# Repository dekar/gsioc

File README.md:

# gsioc
OpenHW Gilson GSIOC controller

This controller is an easier method to connect your Gilson GSIOC devices with PC.

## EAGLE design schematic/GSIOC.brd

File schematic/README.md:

File in Cadsoft Eagle format
ver 0.5

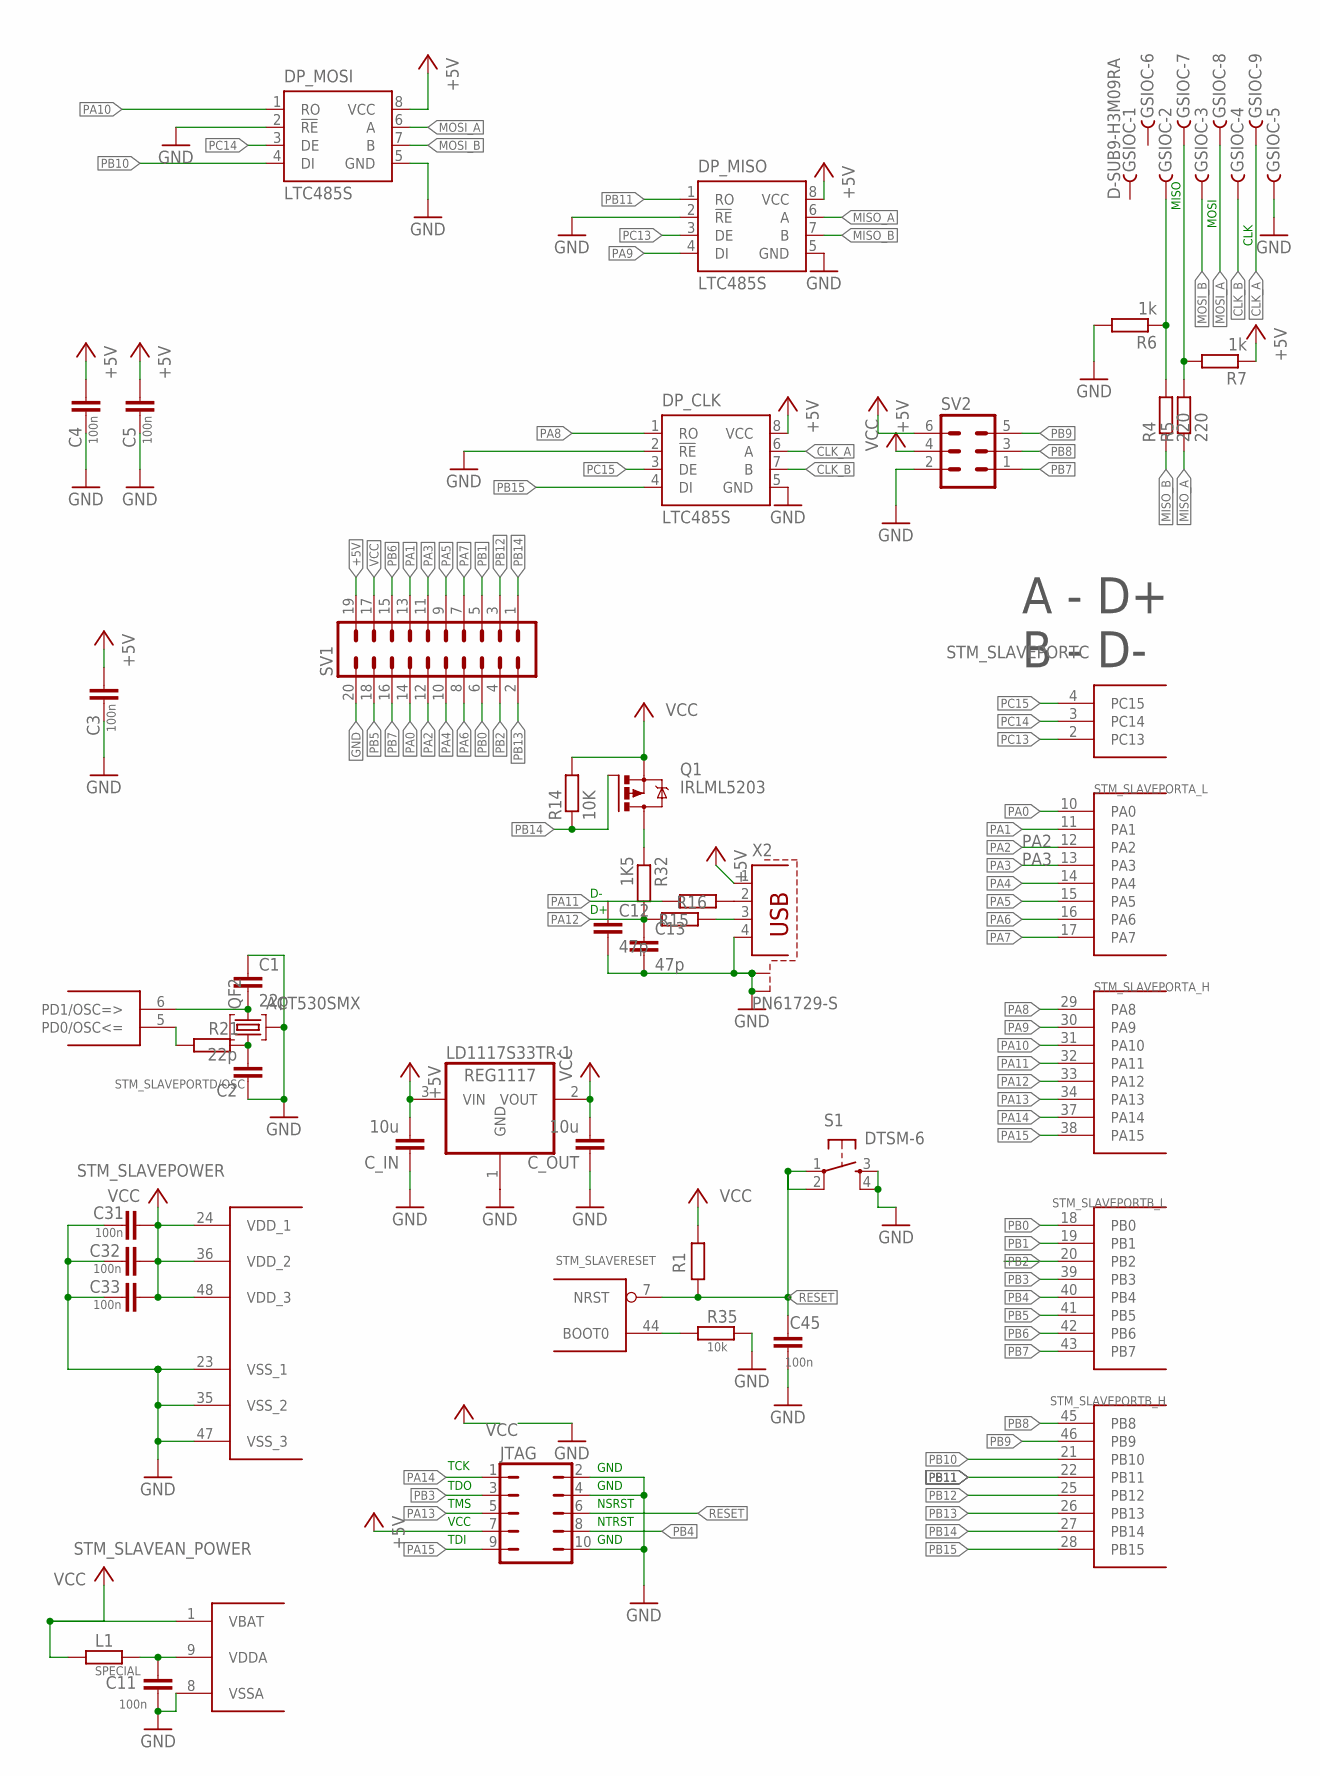
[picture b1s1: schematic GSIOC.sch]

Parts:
C1, C2: 22p; C0805
C3, C11, C31, C32, C33: 100n; C0805
C4, C5, C45: 100n; C0805K
C12, C13: 47p; C0805K
C_IN: 10u; C0805K
C_OUT: 10u; C0805K
DP_CLK: LTC485S; SOIC8
DP_MISO: LTC485S; SOIC8
DP_MOSI: LTC485S; SOIC8
GSIOC: D-SUB9-H3M09RA; H3M09RA
JTAG: JP5Q
L1: SPECIAL; M0805
LD1117S33TR-1: REG1117; SOT223
Q1: IRLML5203; MICRO3
QF2: ACT530SMX; ACT_530SMX
R1: 5k; M0805
R4, R5: 220; M0805
R6, R7: 1k; M0805
R14: 10K; M0805
R15, R16: 22; M0805
R21: R-EU_M0805; M0805
R32: 1K5; M0805
R35: 10k; M0805
S1: DTSM-6
STM_SLAVE: STM32F10XCXT6; TQFP48
SV1: ML20L
SV2: ML6L
X2: PN61729-S

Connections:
+5V: C3.1, C4.1, C5.1, C_IN.2, DP_CLK.8 (VCC), DP_MISO.8 (VCC), DP_MOSI.8 (VCC), JTAG.7, LD1117S33TR-1.3 (VIN), R7.1, SV1.19, SV2.6, X2.1
CLK_A: DP_CLK.6 (A), GSIOC.9
CLK_B: DP_CLK.7 (B), GSIOC.4
GND: C1.1, C2.1, C3.2, C4.2, C5.2, C11.2, C12.2, C13.2, C31.2, C32.2, C33.2, C45.2, C_IN.1, C_OUT.1, DP_CLK.2 (!RE), DP_CLK.5 (GND), DP_MISO.2 (!RE), DP_MISO.5 (GND), DP_MOSI.2 (!RE), DP_MOSI.5 (GND), GSIOC.5, JTAG.2, JTAG.4, JTAG.10, LD1117S33TR-1.1 (GND), QF2.S$1 (SHLD), QF2.S$2 (SHLD), R6.2, R35.2, S1.3, S1.4, STM_SLAVE.8 (VSSA), STM_SLAVE.23 (VSS_1), STM_SLAVE.35 (VSS_2), STM_SLAVE.47 (VSS_3), SV1.20, SV2.2, X2.4, X2.S1, X2.S2
MISO_A: DP_MISO.6 (A), R5.1
MISO_B: DP_MISO.7 (B), R4.1
MOSI_A: DP_MOSI.6 (A), GSIOC.8
MOSI_B: DP_MOSI.7 (B), GSIOC.3
unnamed: C11.1, L1.2, STM_SLAVE.9 (VDDA)
unnamed: GSIOC.2, R4.2, R6.1
unnamed: GSIOC.7, R5.2, R7.2
unnamed: R35.1, STM_SLAVE.44 (BOOT0)
unnamed: R16.1, X2.2
unnamed: Q1.3 (D), R32.1
unnamed: R15.1, X2.3
unnamed: C2.2, QF2.P1 (1), R21.1
OSC<=: R21.2, STM_SLAVE.5 (PD0/OSC<=)
OSC=>: C1.2, QF2.P2 (2), STM_SLAVE.6 (PD1/OSC=>)
PA0: STM_SLAVE.10 (PA0), SV1.14
PA1: STM_SLAVE.11 (PA1), SV1.13
PA2: STM_SLAVE.12 (PA2), SV1.12
PA3: STM_SLAVE.13 (PA3), SV1.11
PA4: STM_SLAVE.14 (PA4), SV1.10
PA5: STM_SLAVE.15 (PA5), SV1.9
PA6: STM_SLAVE.16 (PA6), SV1.8
PA7: STM_SLAVE.17 (PA7), SV1.7
PA8: DP_CLK.1 (RO), STM_SLAVE.29 (PA8)
PA9: DP_MISO.4 (DI), STM_SLAVE.30 (PA9)
PA10: DP_MOSI.1 (RO), STM_SLAVE.31 (PA10)
PA11: C12.1, R16.2, STM_SLAVE.32 (PA11)
PA12: C13.1, R15.2, R32.2, STM_SLAVE.33 (PA12)
PA13: JTAG.5, STM_SLAVE.34 (PA13)
PA14: JTAG.1, STM_SLAVE.37 (PA14)
PA15: JTAG.9, STM_SLAVE.38 (PA15)
PB0: STM_SLAVE.18 (PB0), SV1.6
PB1: STM_SLAVE.19 (PB1), SV1.5
PB2: STM_SLAVE.20 (PB2), SV1.4
PB3: JTAG.3, STM_SLAVE.39 (PB3)
PB4: JTAG.8, STM_SLAVE.40 (PB4)
PB5: STM_SLAVE.41 (PB5), SV1.18
PB6: STM_SLAVE.42 (PB6), SV1.15
PB7: STM_SLAVE.43 (PB7), SV1.16, SV2.1
PB8: STM_SLAVE.45 (PB8), SV2.3
PB9: STM_SLAVE.46 (PB9), SV2.5
PB10: DP_MOSI.4 (DI), STM_SLAVE.21 (PB10)
PB11: DP_MISO.1 (RO), STM_SLAVE.22 (PB11)
PB12: STM_SLAVE.25 (PB12), SV1.3
PB13: STM_SLAVE.26 (PB13), SV1.2
PB14: Q1.1 (G), R14.1, STM_SLAVE.27 (PB14), SV1.1
PB15: DP_CLK.4 (DI), STM_SLAVE.28 (PB15)
PC13: DP_MISO.3 (DE), STM_SLAVE.2 (PC13)
PC14: DP_MOSI.3 (DE), STM_SLAVE.3 (PC14)
PC15: DP_CLK.3 (DE), STM_SLAVE.4 (PC15)
RESET: C45.1, JTAG.6, R1.2, S1.1, S1.2, STM_SLAVE.7 (NRST)
VCC: C31.1, C32.1, C33.1, C_OUT.2, L1.1, LD1117S33TR-1.2 (VOUT), Q1.2 (S), R1.1, R14.2, STM_SLAVE.1 (VBAT), STM_SLAVE.24 (VDD_1), STM_SLAVE.36 (VDD_2), STM_SLAVE.48 (VDD_3), SV1.17, SV2.4

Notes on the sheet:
TCK
TDO
TMS
VCC
TDI
GND
NSRST
NTRST
A - D+ B - D-
MISO
MOSI
CLK

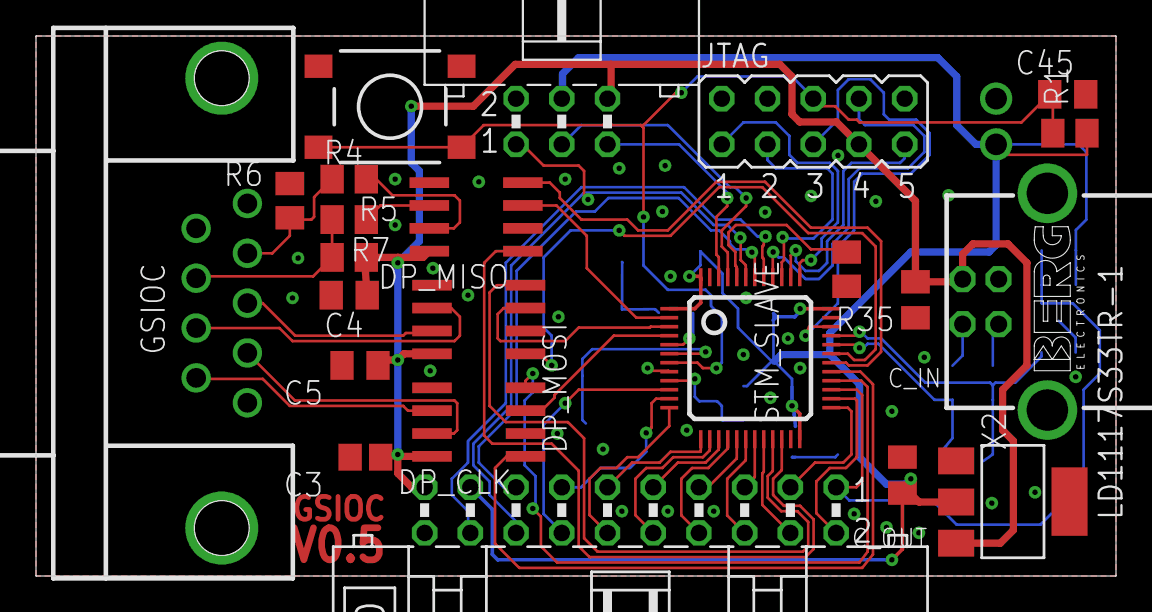
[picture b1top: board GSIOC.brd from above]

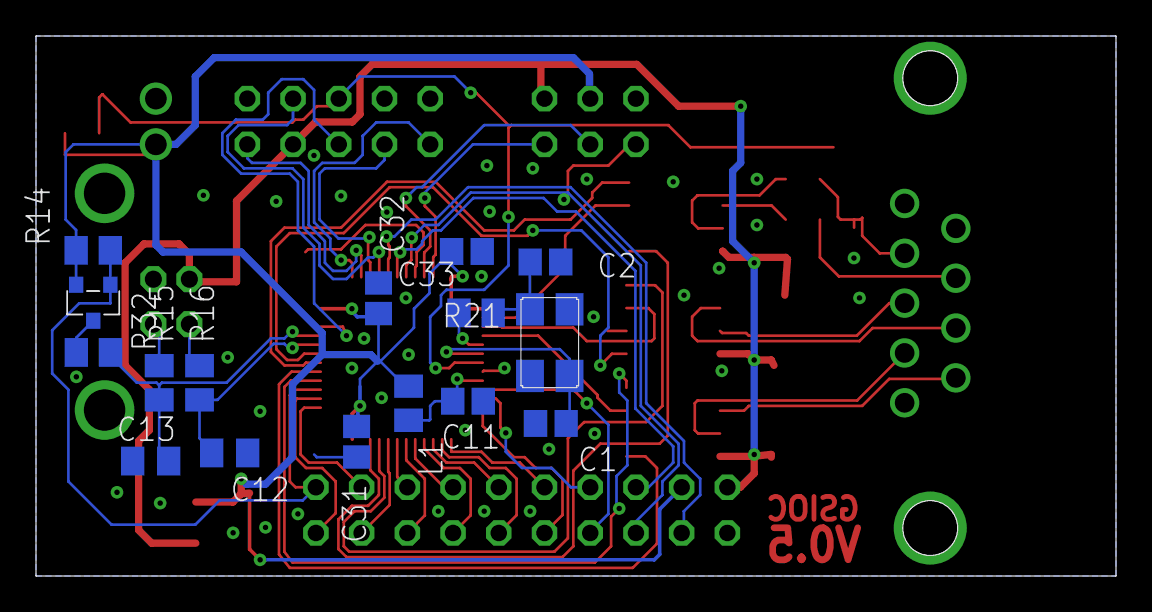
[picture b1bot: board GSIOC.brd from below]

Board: 2 copper layers, 60.0 x 30.0 mm, 39 parts (16 on the bottom side), 55 nets.

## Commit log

2015-04-16 preGH
2015-04-16 add HW
2015-04-16 Add license
2015-06-08 cd /home/dekar/eagle/peptidatorV0.51
2015-06-08 HW version 0.5. Firmware - 0.51. All seems to work
2015-07-07 Work OK whith hw 0.5. Only VCP mode
2021-03-10 last C::B
